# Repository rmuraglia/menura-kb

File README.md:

# menura

The menura is a 30 to 36 key wireless split MX keyboard compatible with the [VIK standard](https://github.com/sadekbaroudi/vik) for modular peripheral device support.

The core concept is a single PCB design which supports *mimicry* of many physical layouts, allowing for non-committal experimentation.
This is accomplished by utilization of overlapping (but not mutually exclusive) switch footprints, and a PCB shape which permits effective conversion to the unibody form factor.

The menura is named for the [lyrebird](https://en.wikipedia.org/wiki/Lyrebird) (scientific name, *menura*), due to its skill in mimicry:

> They are most notable for their impressive ability to mimic natural and artificial sounds from their environment  
> [...]  
> It is one of the world's largest songbirds, and is renowned for its elaborate tail and courtship displays, and its excellent mimicry.

# Design goals

The primary design goal was to create a PCB that would allow you to seamlessly switch between and try out many layouts, gradually reducing your keycount from a 3x5+3 layout like on the [5 column ffkb](https://fingerpunch.xyz/product-tag/ffkb/), to 3x5+2 like the [sweep](https://github.com/davidphilipbarr/Sweep), then eventually a 23332+2 like the [hummingbird](https://github.com/PJE66/hummingbird).  
In parallel to the keycount flexibility, I also wanted it to be easy to try out both a true split layout as well as unibody layouts ranging from the aggressively angled like the [barobord](https://github.com/sadekbaroudi/barobord) to more relaxed angles like the [duet](https://github.com/zzeneg/duet).

To accomplish this goal, the menura has two key features:

## Partially overlapping switch footprints

By carefully arranging switch footprints, we can set it up such that *all* hotswap sockets can be soldered without interfering with each other.  
This allows you to defer the choice of layout to case assembly time rather than being forced to commit irreversibly at PCB build time, encouraging experimentation.

This requires a concession to use MX switches only.
Reduced choc spacing and the shape of choc hotswap sockets make simultaneous installation of all switch sockets impossible (at least without compromising on switch rotation, which impacts keycap compatibility, etc).

## MCU relocation and unibody wedges

To allow for effective and flexible unibody conversion, the MCUs needed to be relocated out of their conventional spot next to the inner index column.
Without this modification, we cannot get the halves close enough together to accurately mimic unibody layouts.

The resulting PCB edge cut enables a case + wedge design that can reproduce a wide range of unibody angles and inter-half distances.  
The case designs in this repo support insertion of magnets into the case walls to allow for simple insertion and removal of the wedges.

## VIK support

Finally, after accomplishing the two previous goals, to lean into the theme of flexibility, versatility and experimentation, we added support for the [VIK standard](https://github.com/sadekbaroudi/vik) for peripheral device support.
This means that with one flat flexible cable (FFC), you can integrate a wide range of add ons, like a nice!view display or a cirque trackpad.

# Building your own menura

To build your own menura:

1. Order PCBs from somewhere like [JLC](https://jlcpcb.com/) using the gerbers in the [releases](https://github.com/rmuraglia/menura-kb/releases) section of this repo
2. Follow the [build guide](/docs/build-guide.md) to:
    1. Solder the PCB
    2. Assemble the case, using a case printed from the [`case/`](/case/) directory
3. Flash the [ZMK studio](https://zmk.dev/docs/features/studio) ready firmware from the [releases](https://github.com/rmuraglia/menura-kb/releases) section of this repo for testing and basic keymap customization
4. If needed (for advanced keymap configuration), write and flash your own ZMK firmware, using the [menura shield module](https://github.com/rmuraglia/zmk-keyboards-menura). The ZMK docs has a page on [modules](https://zmk.dev/docs/features/modules), for more details on using modules

If you want to quickly inspect the PCB or schematic to debug something or further understand the design, you can quickly view these in browser with kicanvas: [menura in kicanvas](https://kicanvas.org/?github=https://github.com/rmuraglia/menura-kb/blob/main/pcb/menura.kicad_pro).  
Tip: in the pcb view, within the sidebar's objects section (with the triangle, circle and square icon), you can turn the slider for "zones" all the way down to stop displaying the ground fill to better see the traces and footprints. 

# Inspiration and references

The board's concept, with flexible key positions and the ability to use two split halves as one whole was inspired heavily by [ErgoTravelXT](https://github.com/FIXMBR/ErgoTravelXT).  
The layouts the menura attempts to mimic include the [ffkb](https://fingerpunch.xyz/product-tag/ffkb/), the [vulpes minora](https://github.com/sadekbaroudi/vulpes-minora), the [sweep](https://github.com/davidphilipbarr/Sweep) and [urchin](https://github.com/duckyb/urchin), the [hummingbird](https://github.com/PJE66/hummingbird), and countless others.

On the design side, I learned a ton on the ergogen side from the [nostrum](https://github.com/bennytrouser/nostrum), [trochilidae](https://github.com/jcmkk3/trochilidae) (rufous and berylline), and [corax](https://github.com/dnlbauer/corax-keyboard) configs, as well as [flatfootfox's guide](https://flatfootfox.com/ergogen-introduction/).  
Other boards I studied on the kicad side include the vulpes minora, urchin, [temper](https://github.com/raeedcho/temper) and [klotz](https://github.com/GEIGEIGEIST/KLOTZ).
zzeneg's [zzkeeb](https://github.com/zzeneg/zzkeeb) library was critical in helping me cut through the endless options for kicad footprints to find an organized and curated set to start with.

# Thanks

I'd like to thank Sadek Baroudi and the members of the [fingerpunch discord](https://discord.gg/ewS6xbCgPb) community, especially Hazel who (unwillingly) taught me everything I know, Saixos and bravekarma for teaching me how to do things right (even if I usually ignored their suggestions), and reeve, damselfly, Yingeling and PyntieHet for celebrating every small step along the way and encouraging me to finish the project.

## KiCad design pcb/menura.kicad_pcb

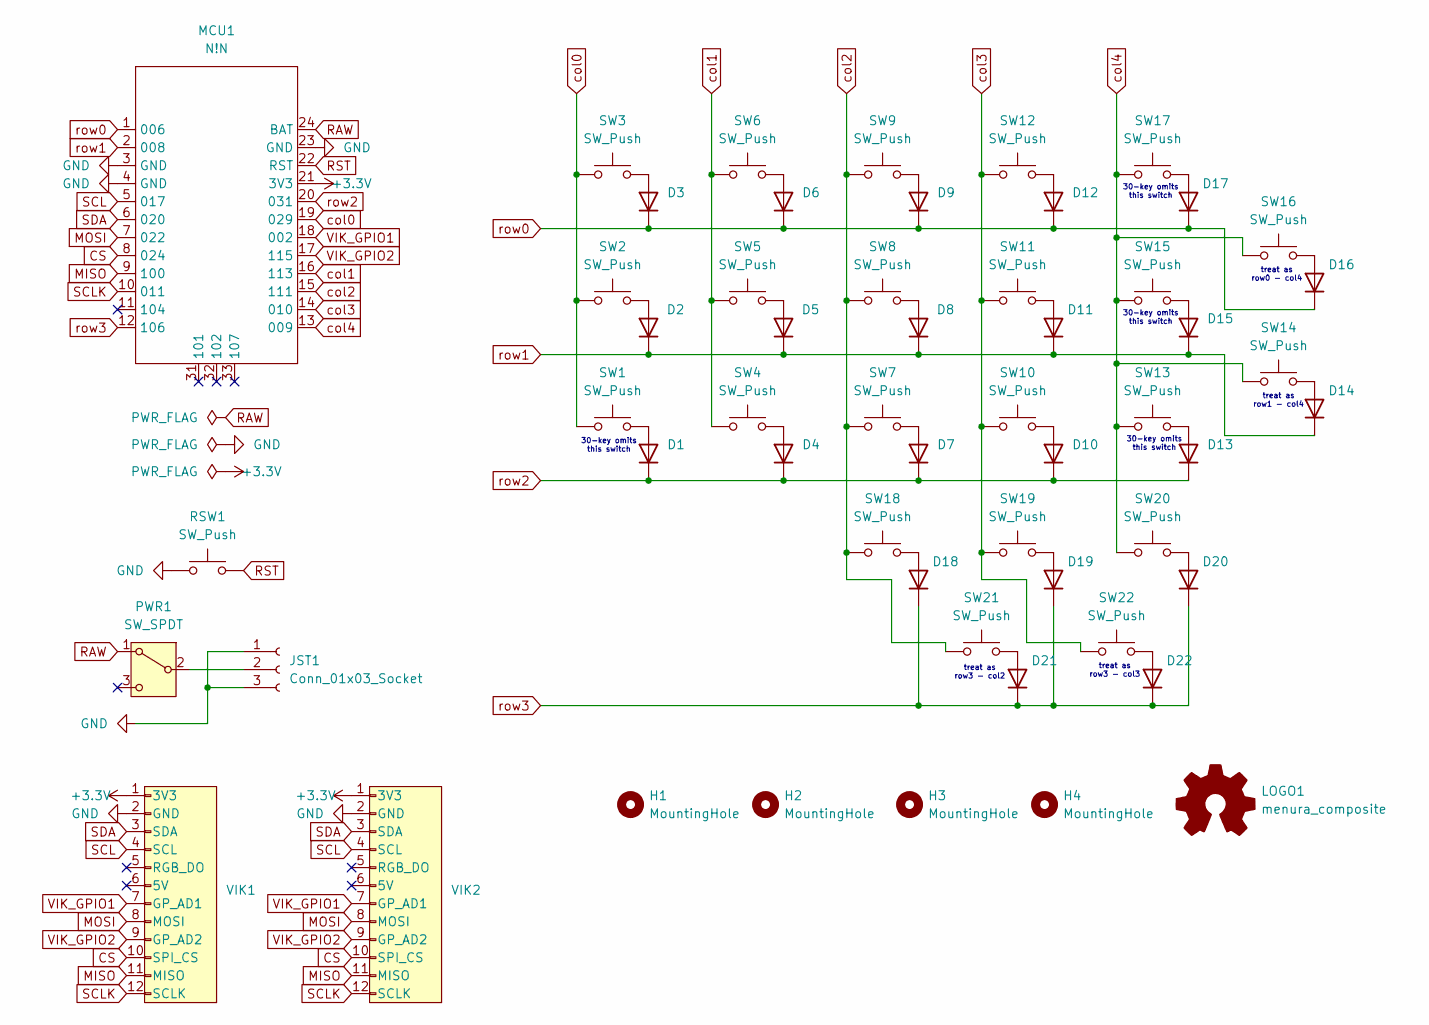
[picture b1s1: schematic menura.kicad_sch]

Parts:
D1, D2, D3, D4, D5, D6, D7, D8, D9, D10, D11, D12, D13, D14, D15, D16, D17, D18, D19, D20, D21, D22: 1N4148W; Diode_SMD-reversible-urchin
H1, H2, H3, H4: MountingHole; MountingHole_3.2mm_M3
JST1: Conn_01x03_Socket; Connector_JST-PH-3prong
LOGO1: menura_composite; Logo_menura_composite
MCU1: N!N; MCU_nice-nano
PWR1: SW_SPDT; Switch_power-reversible-kim
RSW1: SW_Push; Switch_reset-2pin
SW1, SW2, SW3, SW4, SW5, SW6, SW7, SW8, SW9, SW10, SW11, SW12, SW13, SW14, SW15, SW16, SW17, SW18, SW19, SW20, SW21, SW22: SW_Push; Switch_MX-hotswap-reversible
VIK1: Connector_vik-keyboard-horizontal
VIK2: Connector_vik-keyboard-throughhole

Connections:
+3.3V: MCU1.21 (3V3), VIK1.1 (3V3), VIK2.1 (3V3)
CS: MCU1.8 (024), VIK1.10 (SPI_CS), VIK2.10 (SPI_CS)
GND: JST1.1, JST1.3, MCU1.3 (GND), MCU1.4 (GND), MCU1.23 (GND), RSW1.1, VIK1.2 (GND), VIK2.2 (GND)
MISO: MCU1.9 (100), VIK1.11 (MISO), VIK2.11 (MISO)
MOSI: MCU1.7 (022), VIK1.8 (MOSI), VIK2.8 (MOSI)
unnamed: D1.2 (A), SW1.2
unnamed: D2.2 (A), SW2.2
unnamed: D3.2 (A), SW3.2
unnamed: D4.2 (A), SW4.2
unnamed: D5.2 (A), SW5.2
unnamed: D6.2 (A), SW6.2
unnamed: D7.2 (A), SW7.2
unnamed: D8.2 (A), SW8.2
unnamed: D9.2 (A), SW9.2
unnamed: D10.2 (A), SW10.2
unnamed: D11.2 (A), SW11.2
unnamed: D12.2 (A), SW12.2
unnamed: D13.2 (A), SW13.2
unnamed: D14.2 (A), SW14.2
unnamed: D15.2 (A), SW15.2
unnamed: D16.2 (A), SW16.2
unnamed: D17.2 (A), SW17.2
unnamed: D18.2 (A), SW18.2
unnamed: D19.2 (A), SW19.2
unnamed: D20.2 (A), SW20.2
unnamed: D21.2 (A), SW21.2
unnamed: D22.2 (A), SW22.2
unnamed: JST1.2, PWR1.2 (B)
RAW: MCU1.24 (BAT), PWR1.1 (A)
RST: MCU1.22 (RST), RSW1.2
SCL: MCU1.5 (017), VIK1.4 (SCL), VIK2.4 (SCL)
SCLK: MCU1.10 (011), VIK1.12 (SCLK), VIK2.12 (SCLK)
SDA: MCU1.6 (020), VIK1.3 (SDA), VIK2.3 (SDA)
VIK_GPIO1: MCU1.18 (002), VIK1.7 (GP_AD1), VIK2.7 (GP_AD1)
VIK_GPIO2: MCU1.17 (115), VIK1.9 (GP_AD2), VIK2.9 (GP_AD2)
col0: MCU1.19 (029), SW1.1, SW2.1, SW3.1
col1: MCU1.16 (113), SW4.1, SW5.1, SW6.1
col2: MCU1.15 (111), SW7.1, SW8.1, SW9.1, SW18.1, SW21.1
col3: MCU1.14 (010), SW10.1, SW11.1, SW12.1, SW19.1, SW22.1
col4: MCU1.13 (009), SW13.1, SW14.1, SW15.1, SW16.1, SW17.1, SW20.1
row0: D3.1 (K), D6.1 (K), D9.1 (K), D12.1 (K), D16.1 (K), D17.1 (K), MCU1.1 (006)
row1: D2.1 (K), D5.1 (K), D8.1 (K), D11.1 (K), D14.1 (K), D15.1 (K), MCU1.2 (008)
row2: D1.1 (K), D4.1 (K), D7.1 (K), D10.1 (K), D13.1 (K), MCU1.20 (031)
row3: D18.1 (K), D19.1 (K), D20.1 (K), D21.1 (K), D22.1 (K), MCU1.12 (106)

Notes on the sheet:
30-key omits this switch
treat as row3 - col3
treat as row3 - col2
treat as row1 - col4
treat as row0 - col4

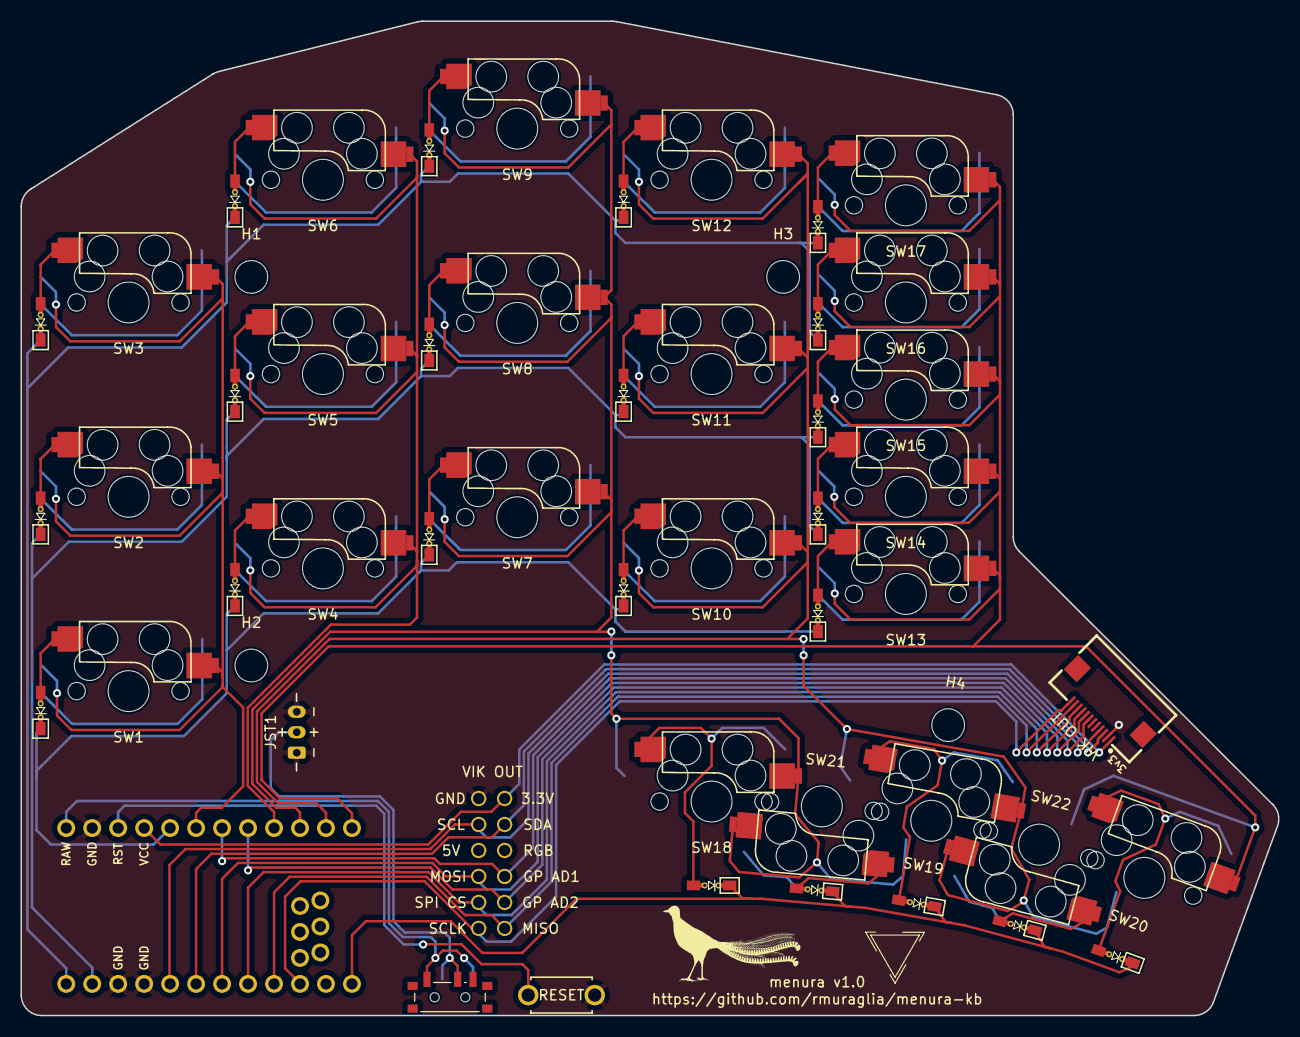
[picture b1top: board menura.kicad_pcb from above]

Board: 2 copper layers, 123.0 x 97.2 mm, 55 parts (0 on the bottom side), 44 nets.

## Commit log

2024-08-31 basic switch footprint layout
2024-08-31 add diodes to pcb
2024-08-31 pcb todos
2024-09-23 preview images
2024-09-23 gitignore
2024-10-02 component placement, schematic
2024-10-03 fix diode ordering
2024-10-03 fix: spi pins should be high freq
2024-10-03 update footprints: centering, pad assignments
2024-10-04 clean up yaml
2024-10-04 iterate on power switch and jst placement
2024-10-04 iterate on vik placement
2024-10-04 more vik footprints
2024-10-04 add vik throughole breakout
2024-10-04 tweak reset button placement
2024-10-04 remove non-local library
2024-10-05 yaml comments
2024-10-05 double sized vik silks
2024-10-06 edge cut wip
2024-10-06 adjust vik position and rotation
2024-10-07 shuffle few components around
2024-10-07 tweak urchin diode footprint, add tenting puck footprints
2024-10-08 logo silkscreens
2024-10-08 holes
2024-10-08 add mounting holes
2024-10-09 one more pth
2024-10-09 remove plated holes on inner edge
2024-10-09 give jst more breathing room
2024-10-09 reorder a few pins
2024-10-09 readme
2024-10-09 reference boards in readme
2024-10-10 bird silhouette logo
2024-10-10 satisfy erc
2024-10-10 regen pcb before routing
2024-10-10 scoot the bird
2024-10-15 routing partially done
2024-10-16 column crossovers
2024-10-16 rough cols 2 and 4
2024-10-17 thumbs sloppy but done
2024-10-17 fiddle with edge cut
2024-10-17 ground fill
2024-10-17 route thumb area
2024-11-23 3x5_3 first case attempt
2024-11-24 15 degree, 2mm wedge
2024-11-24 update sketches
2024-11-24 update fusion
2024-11-24 update step
2024-11-24 update stls
2024-11-24 more vertical allowance for usb (right side is lower)
2024-11-25 tiny gap in dxf
2024-11-25 add thummingbird and urchin outlines
2024-11-26 more cleaned up outlines
2024-12-14 start build guide
2024-12-14 add more case dxfs
2024-12-14 few image details
2024-12-14 jpg not png
2024-12-14 Fix warning alert box
2024-12-14 more tips
2024-12-14 mcu examples
2024-12-15 links to collpased sections dont work well
2024-12-16 photos of complete pcb
2024-12-17 case doc wip
2024-12-17 more case docs
2024-12-18 more case design, up to component cutouts
2024-12-18 sketch pictures
2024-12-18 case guide done (?)
2024-12-19 firmware info
2024-12-21 few more notes
2024-12-21 build guide and case docs
2024-12-21 rename plate -> top
2024-12-21 add hummingbird case files
2024-12-21 add hummingbird case stls
2024-12-22 revise 3x5_3 case
2024-12-22 revise wedge
2024-12-22 change wedge naming convention
2024-12-22 sharp angle wedge
2024-12-22 relaxed angle wedge
2024-12-22 relaxed, wide wedge
2024-12-22 case top variants with no reset button hole
2024-12-23 23332_3 cases
2024-12-23 close face in sketch
2024-12-23 add 3x5_2 cases
2024-12-23 Add CERN-OHL-S LICENSE
2024-12-25 cirque wedge
2024-12-26 reorg readme
2024-12-26 readme tweak
2024-12-26 clarify alt layout wording
2024-12-26 note on zmk studio ready firmware
2024-12-28 github handles
2024-12-28 Revert "github handles"
    This reverts commit 1c4ee1c8bd20e77c2fd98d919430c2896d93b7a4.
2024-12-28 33332_3 case
2025-01-09 fix typo in battery images
2025-01-09 info on getting into bootloader
2025-01-09 bootloader entry via hold tap instead of tap dance
2025-01-09 add sample build pictures
2025-01-09 vertical orientation for build collage
2025-01-09 more thanks
2025-01-10 note on controller soldering
2025-02-25 more case outlines
2025-02-25 outline for pyntie too
2025-03-08 23333_3 outlines
2025-03-11 23333_3 case for autoferrit
